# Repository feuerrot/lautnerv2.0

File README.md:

### What?
Well, we wanted some kit for the next CCC events like the 30C3. I had no
real idea for something new and there was this piece of art, called
*werdeteildesgesamtwiderstand* which produces a tone based on how much you
are pressing on two pads.

The circuit is very simple and it makes noise. So it's perfect for people
who make their first experiences with soldering because there are not a lot
of parts, you get an instant feedback and there are pads on the backside so
you can modify it on your own!

Also it should be easy to supply it and targeting some nerds there was only
one simple solution: USB. And because there are additional pads for VCC and
GND you can also solder some 9V battery connector there.

### Images
#### Circuit

#### Board

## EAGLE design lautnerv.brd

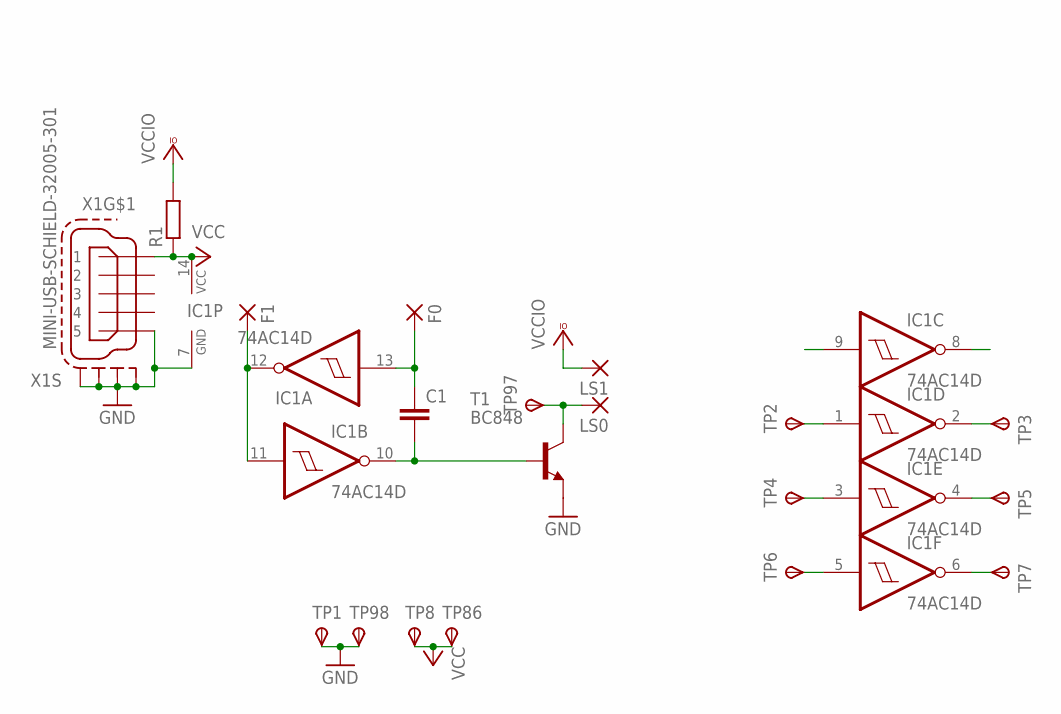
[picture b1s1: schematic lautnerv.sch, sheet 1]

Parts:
C1: C-EUC1206K; C1206K
F0, F1: SMD5; SMD2,54-5,08
IC1: 74AC14D; SO14
LS0, LS1: SMD5; SMD2,54-5,08
R1: R-EU_M1206; M1206
T1: BC848; SOT23
TP1, TP2, TP3, TP4, TP5, TP6, TP7, TP8, TP86, TP97, TP98: TPSTP12SQ; TP12SQ
X1: MINI-USB-SCHIELD-32005-301; 32005-301

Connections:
F0: F1.1, IC1.11 (I), IC1.12 (O)
F1: C1.1, F0.1, IC1.13 (I)
GND: IC1.7 (GND), T1.2 (E), TP1.TP, TP98.TP, X1.5, X1.M1 (S1), X1.M2 (S2), X1.M3 (S3), X1.M4 (S4)
unnamed: LS0.1, T1.3 (C), TP97.TP
unnamed: C1.2, IC1.10 (O), T1.1 (B)
unnamed: IC1.2 (O), TP3.TP
unnamed: IC1.4 (O), TP5.TP
unnamed: IC1.6 (O), TP7.TP
unnamed: IC1.1 (I), TP2.TP
unnamed: IC1.3 (I), TP4.TP
unnamed: IC1.5 (I), TP6.TP
VCC: IC1.14 (VCC), R1.1, TP8.TP, TP86.TP, X1.1
VCCIO: LS1.1, R1.2

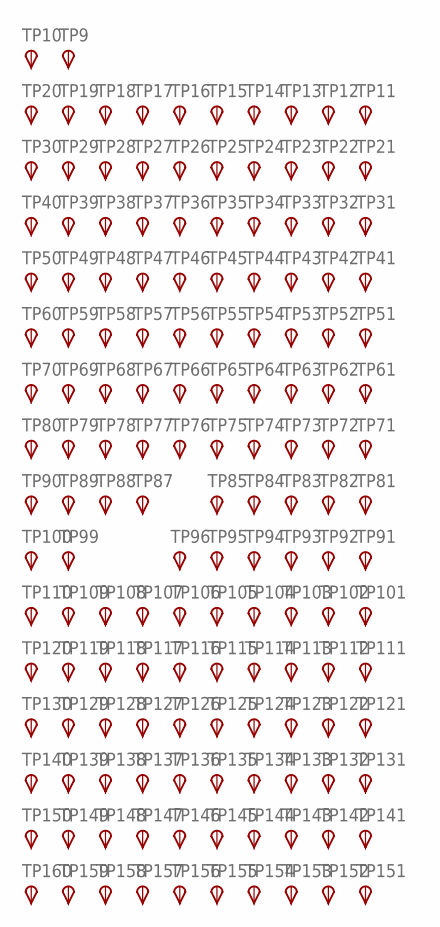
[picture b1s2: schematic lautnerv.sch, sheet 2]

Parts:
TP9, TP10, TP11, TP12, TP13, TP14, TP15, TP16, TP17, TP18, TP19, TP20, TP21, TP22, TP23, TP24, TP25, TP26, TP27, TP28, TP29, TP30, TP31, TP32, TP33, TP34, TP35, TP36, TP37, TP38, TP39, TP40, TP41, TP42, TP43, TP44, TP45, TP46, TP47, TP48, TP49, TP50, TP51, TP52, TP53, TP54, TP55, TP56, TP57, TP58, TP59, TP60, TP61, TP62, TP63, TP64, TP65, TP66, TP67, TP68, TP69, TP70, TP71, TP72, TP73, TP74, TP75, TP76, TP77, TP78, TP79, TP80, TP81, TP82, TP83, TP84, TP85, TP87, TP88, TP89, TP90, TP91, TP92, TP93, TP94, TP95, TP96, TP99, TP100, TP101, TP102, TP103, TP104, TP105, TP106, TP107, TP108, TP109, TP110, TP111, TP112, TP113, TP114, TP115, TP116, TP117, TP118, TP119, TP120, TP121, TP122, TP123, TP124, TP125, TP126, TP127, TP128, TP129, TP130, TP131, TP132, TP133, TP134, TP135, TP136, TP137, TP138, TP139, TP140, TP141, TP142, TP143, TP144, TP145, TP146, TP147, TP148, TP149, TP150, TP151, TP152, TP153, TP154, TP155, TP156, TP157, TP158, TP159, TP160: TPSTP12SQ; TP12SQ

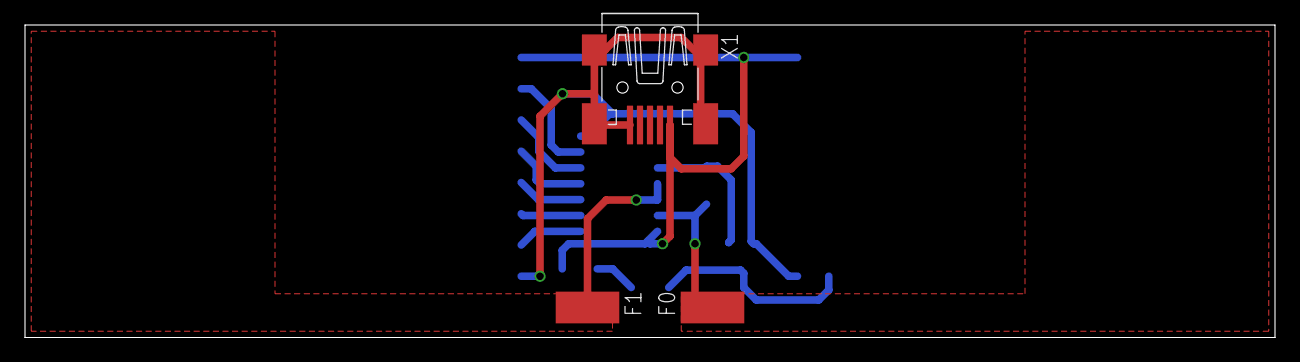
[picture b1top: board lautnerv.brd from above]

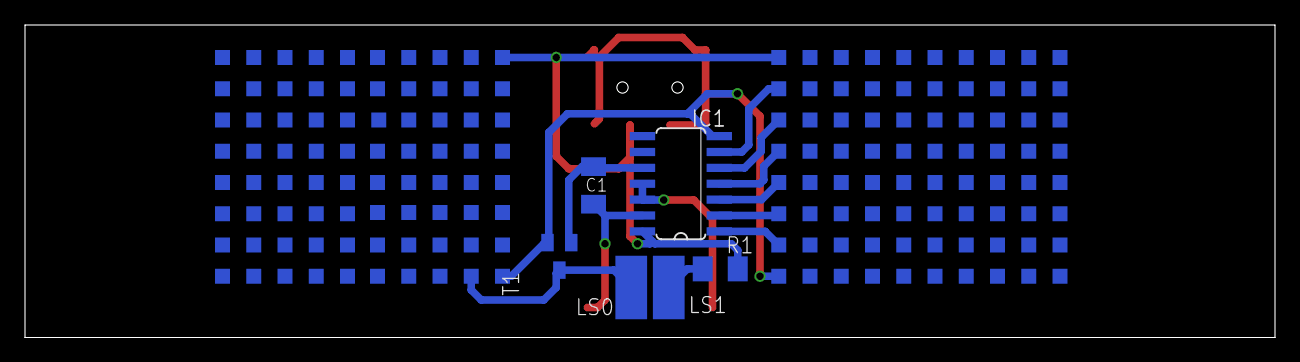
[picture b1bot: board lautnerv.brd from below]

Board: 2 copper layers, 100.0 x 25.0 mm, 169 parts (166 on the bottom side), 13 nets.

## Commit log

2013-06-07 adding readme
2013-06-07 adding images
2013-06-07 moving all the testpads to another page
2013-06-07 Well, the gif was not good…
